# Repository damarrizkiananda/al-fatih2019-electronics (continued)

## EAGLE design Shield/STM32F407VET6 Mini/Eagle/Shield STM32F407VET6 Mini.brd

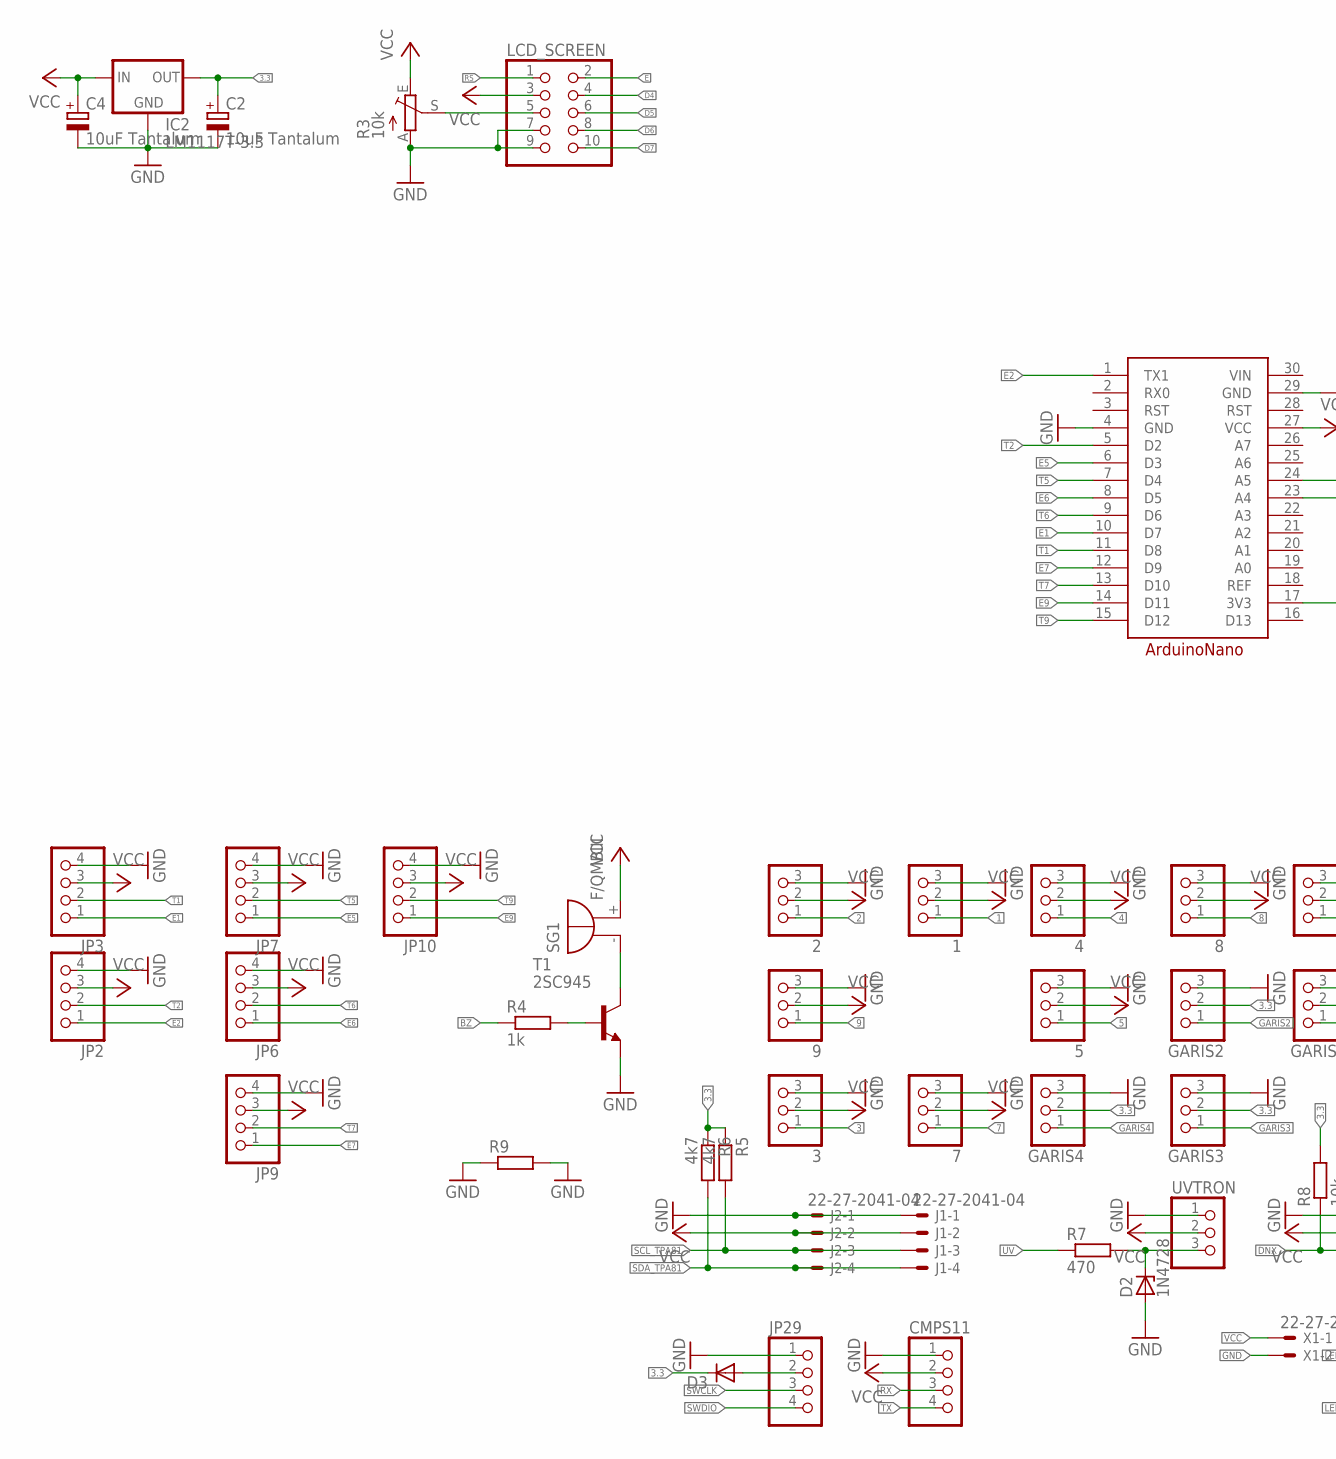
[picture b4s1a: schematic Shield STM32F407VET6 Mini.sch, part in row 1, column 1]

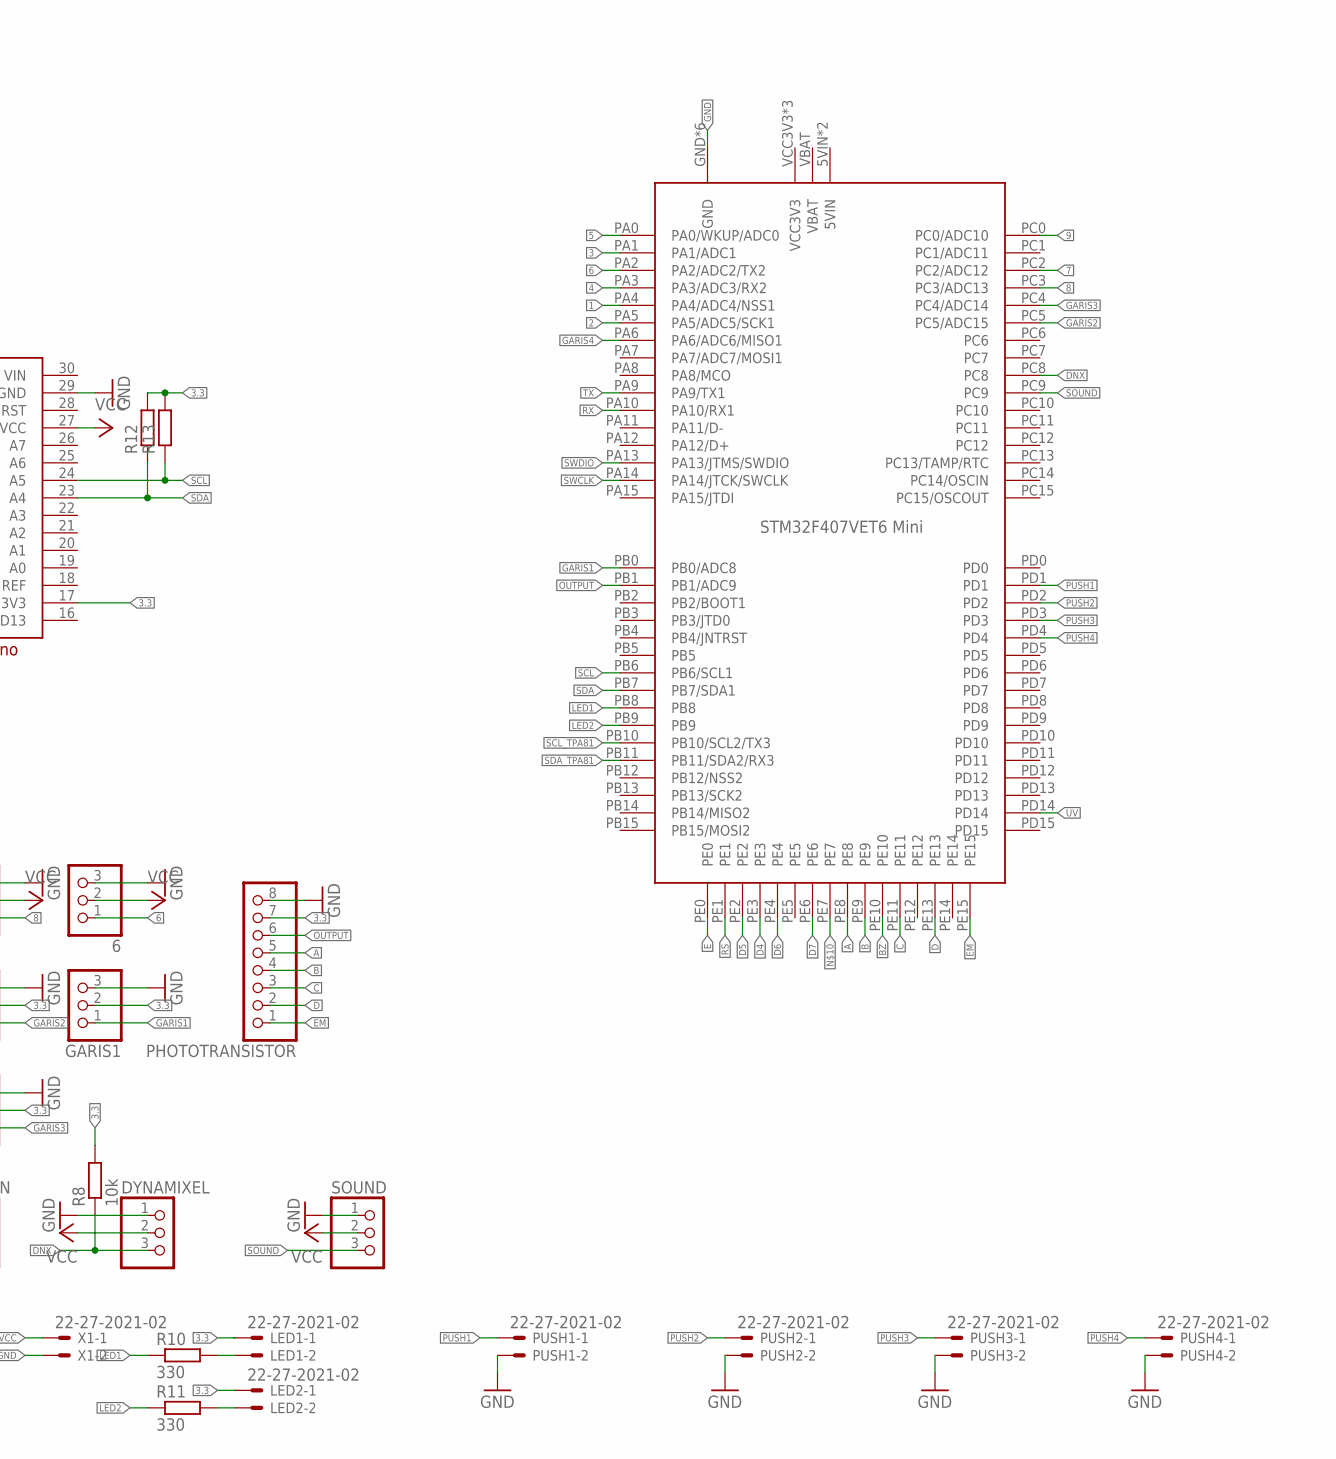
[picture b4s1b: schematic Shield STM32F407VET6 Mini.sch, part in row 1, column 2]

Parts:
1, 2, 3, 4, 5, 6, 7, 8, 9: PINHD-1X3; 1X03
A1: ARDUINONANO
C2, C4: 10uF Tantalum; E2,5-5
CMPS11: PINHD-1X4; 1X04
D2: 1N4728; ZDIO-7.5
D3: DIODE-DO34-7; DO34-7
DYNAMIXEL: PINHD-1X3; 1X03
GARIS1, GARIS2, GARIS3, GARIS4: PINHD-1X3; 1X03
IC2: LM1117T-3.3; TO220
J1, J2: 22-27-2041-04; 6410-04
JP2, JP3, JP6, JP7, JP9, JP10, JP29: PINHD-1X4; 1X04
LCD_SCREEN: PINHD-2X5; 2X05
LED1, LED2: 22-27-2021-02; 6410-02
PHOTOTRANSISTOR: PINHD-1X8; 1X08
PUSH1, PUSH2, PUSH3, PUSH4: 22-27-2021-02; 6410-02
R3: 10k; CA6V
R4: 1k; 0204/7
R5, R6: 4k7; 0204/7
R7: 470; 0204/7
R8: 10k; 0204/7
R9: R-EU_0204/5; 0204/5
R10, R11: 330; M1206
R12, R13: R-EU_0204/7; 0204/7
SG1: F/QMBIII
SOUND: PINHD-1X3; 1X03
T1: 2SC945; TO92-ECB
U$2: STM32F407VET6_MINI
UVTRON: PINHD-1X3; 1X03
X1: 22-27-2021-02; 6410-02

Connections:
1: 1.1, U$2.PA4 (PA4/ADC4/NSS1)
2: 2.1, U$2.PA5 (PA5/ADC5/SCK1)
3: 3.1, U$2.PA1 (PA1/ADC1)
3.3: A1.17 (3V3), C2.+, D3.C, GARIS1.2, GARIS2.2, GARIS3.2, GARIS4.2, IC2.2 (OUT), LED1.1, LED2.1, PHOTOTRANSISTOR.7, R5.1, R6.1, R8.2, R12.2, R13.2
4: 4.1, U$2.PA3 (PA3/ADC3/RX2)
5: 5.1, U$2.PA0 (PA0/WKUP/ADC0)
6: 6.1, U$2.PA2 (PA2/ADC2/TX2)
7: 7.1, U$2.PC2 (PC2/ADC12)
8: 8.1, U$2.PC3 (PC3/ADC13)
9: 9.1, U$2.PC0 (PC0/ADC10)
A: PHOTOTRANSISTOR.5, U$2.PE8
B: PHOTOTRANSISTOR.4, U$2.PE9
BZ: R4.1, U$2.PE10
C: PHOTOTRANSISTOR.3, U$2.PE11
D: PHOTOTRANSISTOR.2, U$2.PE13
D4: LCD_SCREEN.4, U$2.PE3
D5: LCD_SCREEN.6, U$2.PE2
D6: LCD_SCREEN.8, U$2.PE4
D7: LCD_SCREEN.10, U$2.PE6
DNX: DYNAMIXEL.3, R8.1, U$2.PC8
E: LCD_SCREEN.2, U$2.PE0
E1: A1.10 (D7), JP3.1
E2: A1.1 (TX1), JP2.1
E5: A1.6 (D3), JP7.1
E6: A1.8 (D5), JP6.1
E7: A1.12 (D9), JP9.1
E9: A1.14 (D11), JP10.1
EM: PHOTOTRANSISTOR.1, U$2.PE15
GARIS1: GARIS1.1, U$2.PB0 (PB0/ADC8)
GARIS2: GARIS2.1, U$2.PC5 (PC5/ADC15)
GARIS3: GARIS3.1, U$2.PC4 (PC4/ADC14)
GARIS4: GARIS4.1, U$2.PA6 (PA6/ADC6/MISO1)
GND: 1.3, 2.3, 3.3, 4.3, 5.3, 6.3, 7.3, 8.3, 9.3, A1.4 (GND), A1.29 (GND), C2.-, C4.-, CMPS11.1, D2.A, DYNAMIXEL.1, GARIS1.3, GARIS2.3, GARIS3.3, GARIS4.3, IC2.1 (GND), J1.1, J2.1, JP2.4, JP3.4, JP6.4, JP7.4, JP9.4, JP10.4, JP29.1, LCD_SCREEN.7, LCD_SCREEN.9, PHOTOTRANSISTOR.8, PUSH1.2, PUSH2.2, PUSH3.2, PUSH4.2, R3.A, R9.1, R9.2, SOUND.1, T1.E, U$2.GND, U$2.GND@1 (GND), U$2.GND@2 (GND), U$2.GND@3 (GND), U$2.GND@4 (GND), U$2.GND@5 (GND), UVTRON.1, X1.2
LED1: R10.1, U$2.PB8
LED2: R11.1, U$2.PB9
unnamed: D3.A, JP29.2
unnamed: LED1.2, R10.2
unnamed: D2.C, R7.2, UVTRON.3
unnamed: LCD_SCREEN.5, R3.S
unnamed: LED2.2, R11.2
unnamed: SG1.- (+), T1.C
unnamed: R4.2, T1.B
OUTPUT: PHOTOTRANSISTOR.6, U$2.PB1 (PB1/ADC9)
PUSH1: PUSH1.1, U$2.PD1
PUSH2: PUSH2.1, U$2.PD2
PUSH3: PUSH3.1, U$2.PD3
PUSH4: PUSH4.1, U$2.PD4
REF: A1.18 (REF)
RS: LCD_SCREEN.1, U$2.PE1
RX: CMPS11.3, U$2.PA10 (PA10/RX1)
SCL: A1.24 (A5), R13.1, U$2.PB6 (PB6/SCL1)
SCL_TPA81: J1.3, J2.3, R5.2, U$2.PB10 (PB10/SCL2/TX3)
SDA: A1.23 (A4), R12.1, U$2.PB7 (PB7/SDA1)
SDA_TPA81: J1.4, J2.4, R6.2, U$2.PB11 (PB11/SDA2/RX3)
SOUND: SOUND.3, U$2.PC9
SWCLK: JP29.3, U$2.PA14 (PA14/JTCK/SWCLK)
SWDIO: JP29.4, U$2.PA13 (PA13/JTMS/SWDIO)
T1: A1.11 (D8), JP3.2
T2: A1.5 (D2), JP2.2
T5: A1.7 (D4), JP7.2
T6: A1.9 (D6), JP6.2
T7: A1.13 (D10), JP9.2
T9: A1.15 (D12), JP10.2
TX: CMPS11.4, U$2.PA9 (PA9/TX1)
UV: R7.1, U$2.PD14
VCC: 1.2, 2.2, 3.2, 4.2, 5.2, 6.2, 7.2, 8.2, 9.2, A1.27 (VCC), C4.+, CMPS11.2, DYNAMIXEL.2, IC2.3 (IN), J1.2, J2.2, JP2.3, JP3.3, JP6.3, JP7.3, JP9.3, JP10.3, LCD_SCREEN.3, R3.E, SG1.+ (-), SOUND.2, UVTRON.2, X1.1
VIN: A1.30 (VIN)

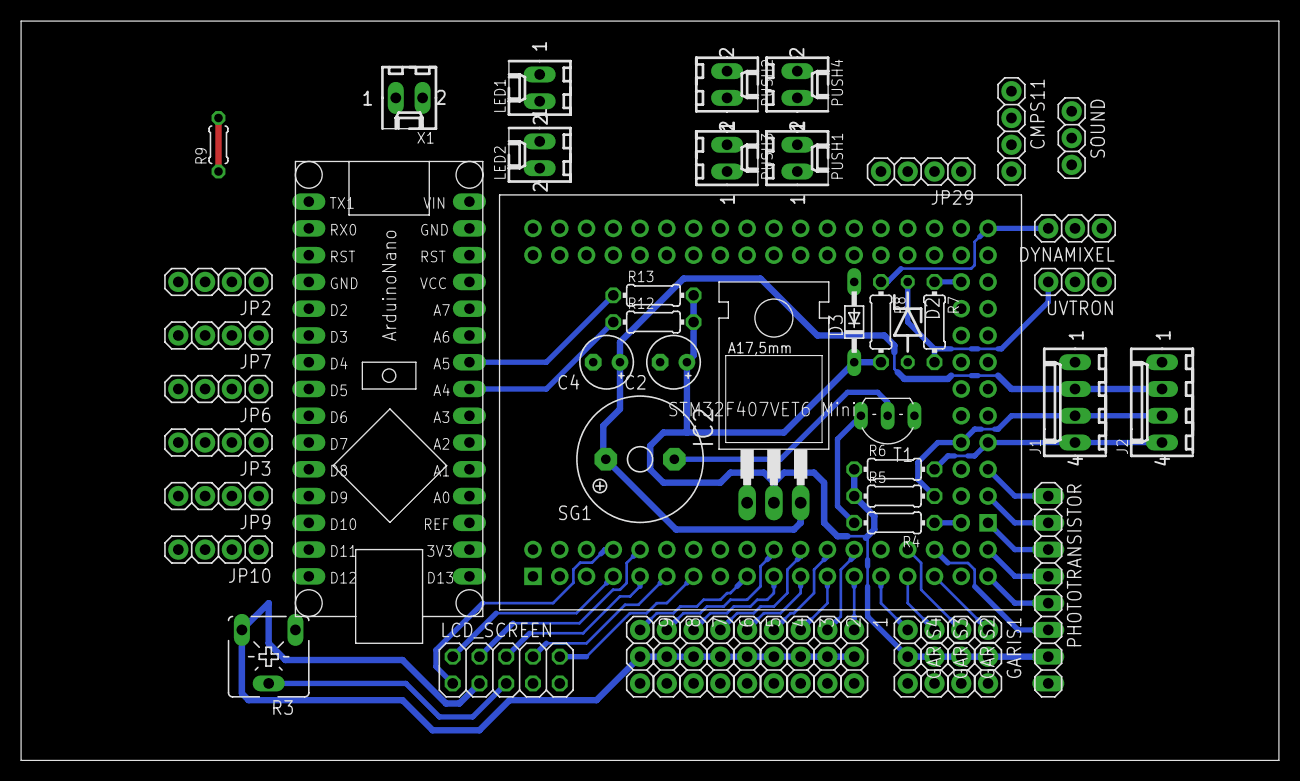
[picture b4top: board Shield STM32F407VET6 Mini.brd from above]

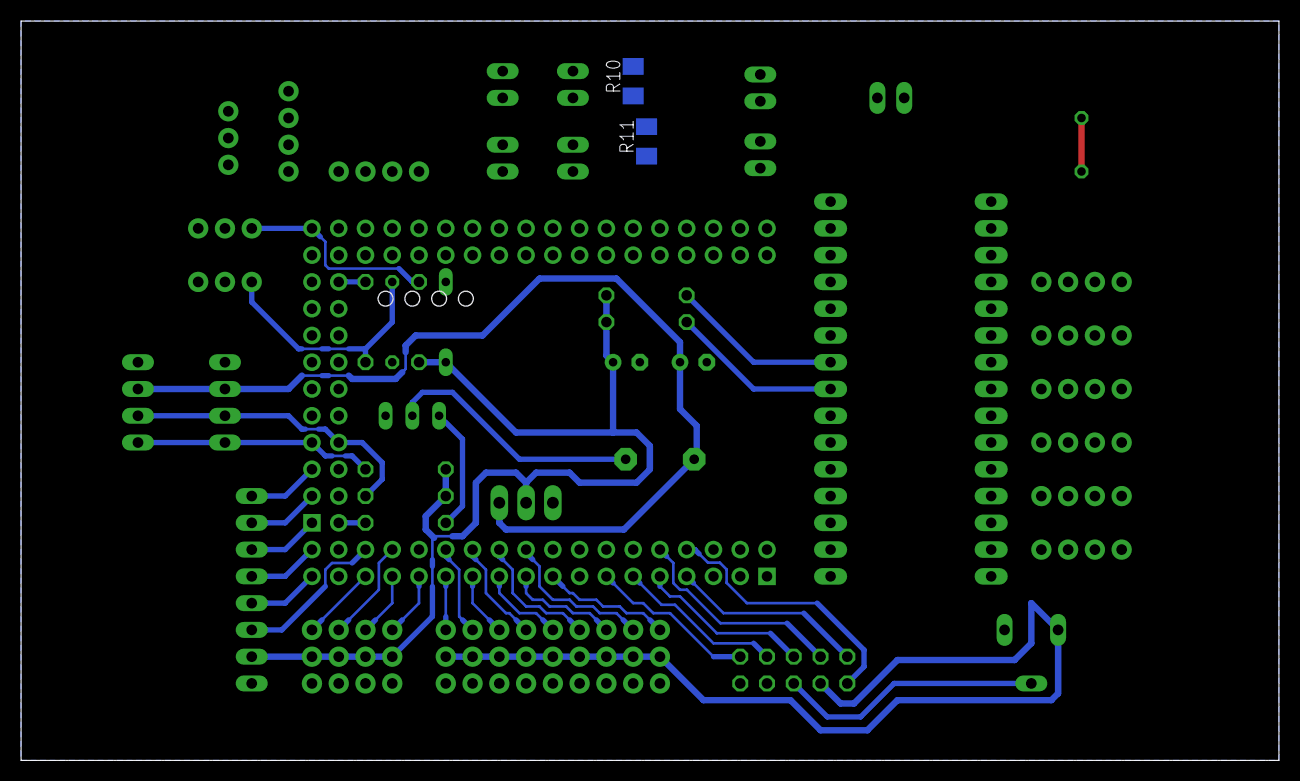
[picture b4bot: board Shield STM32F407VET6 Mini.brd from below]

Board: 2 copper layers, 119.4 x 70.2 mm, 55 parts (2 on the bottom side), 65 nets.

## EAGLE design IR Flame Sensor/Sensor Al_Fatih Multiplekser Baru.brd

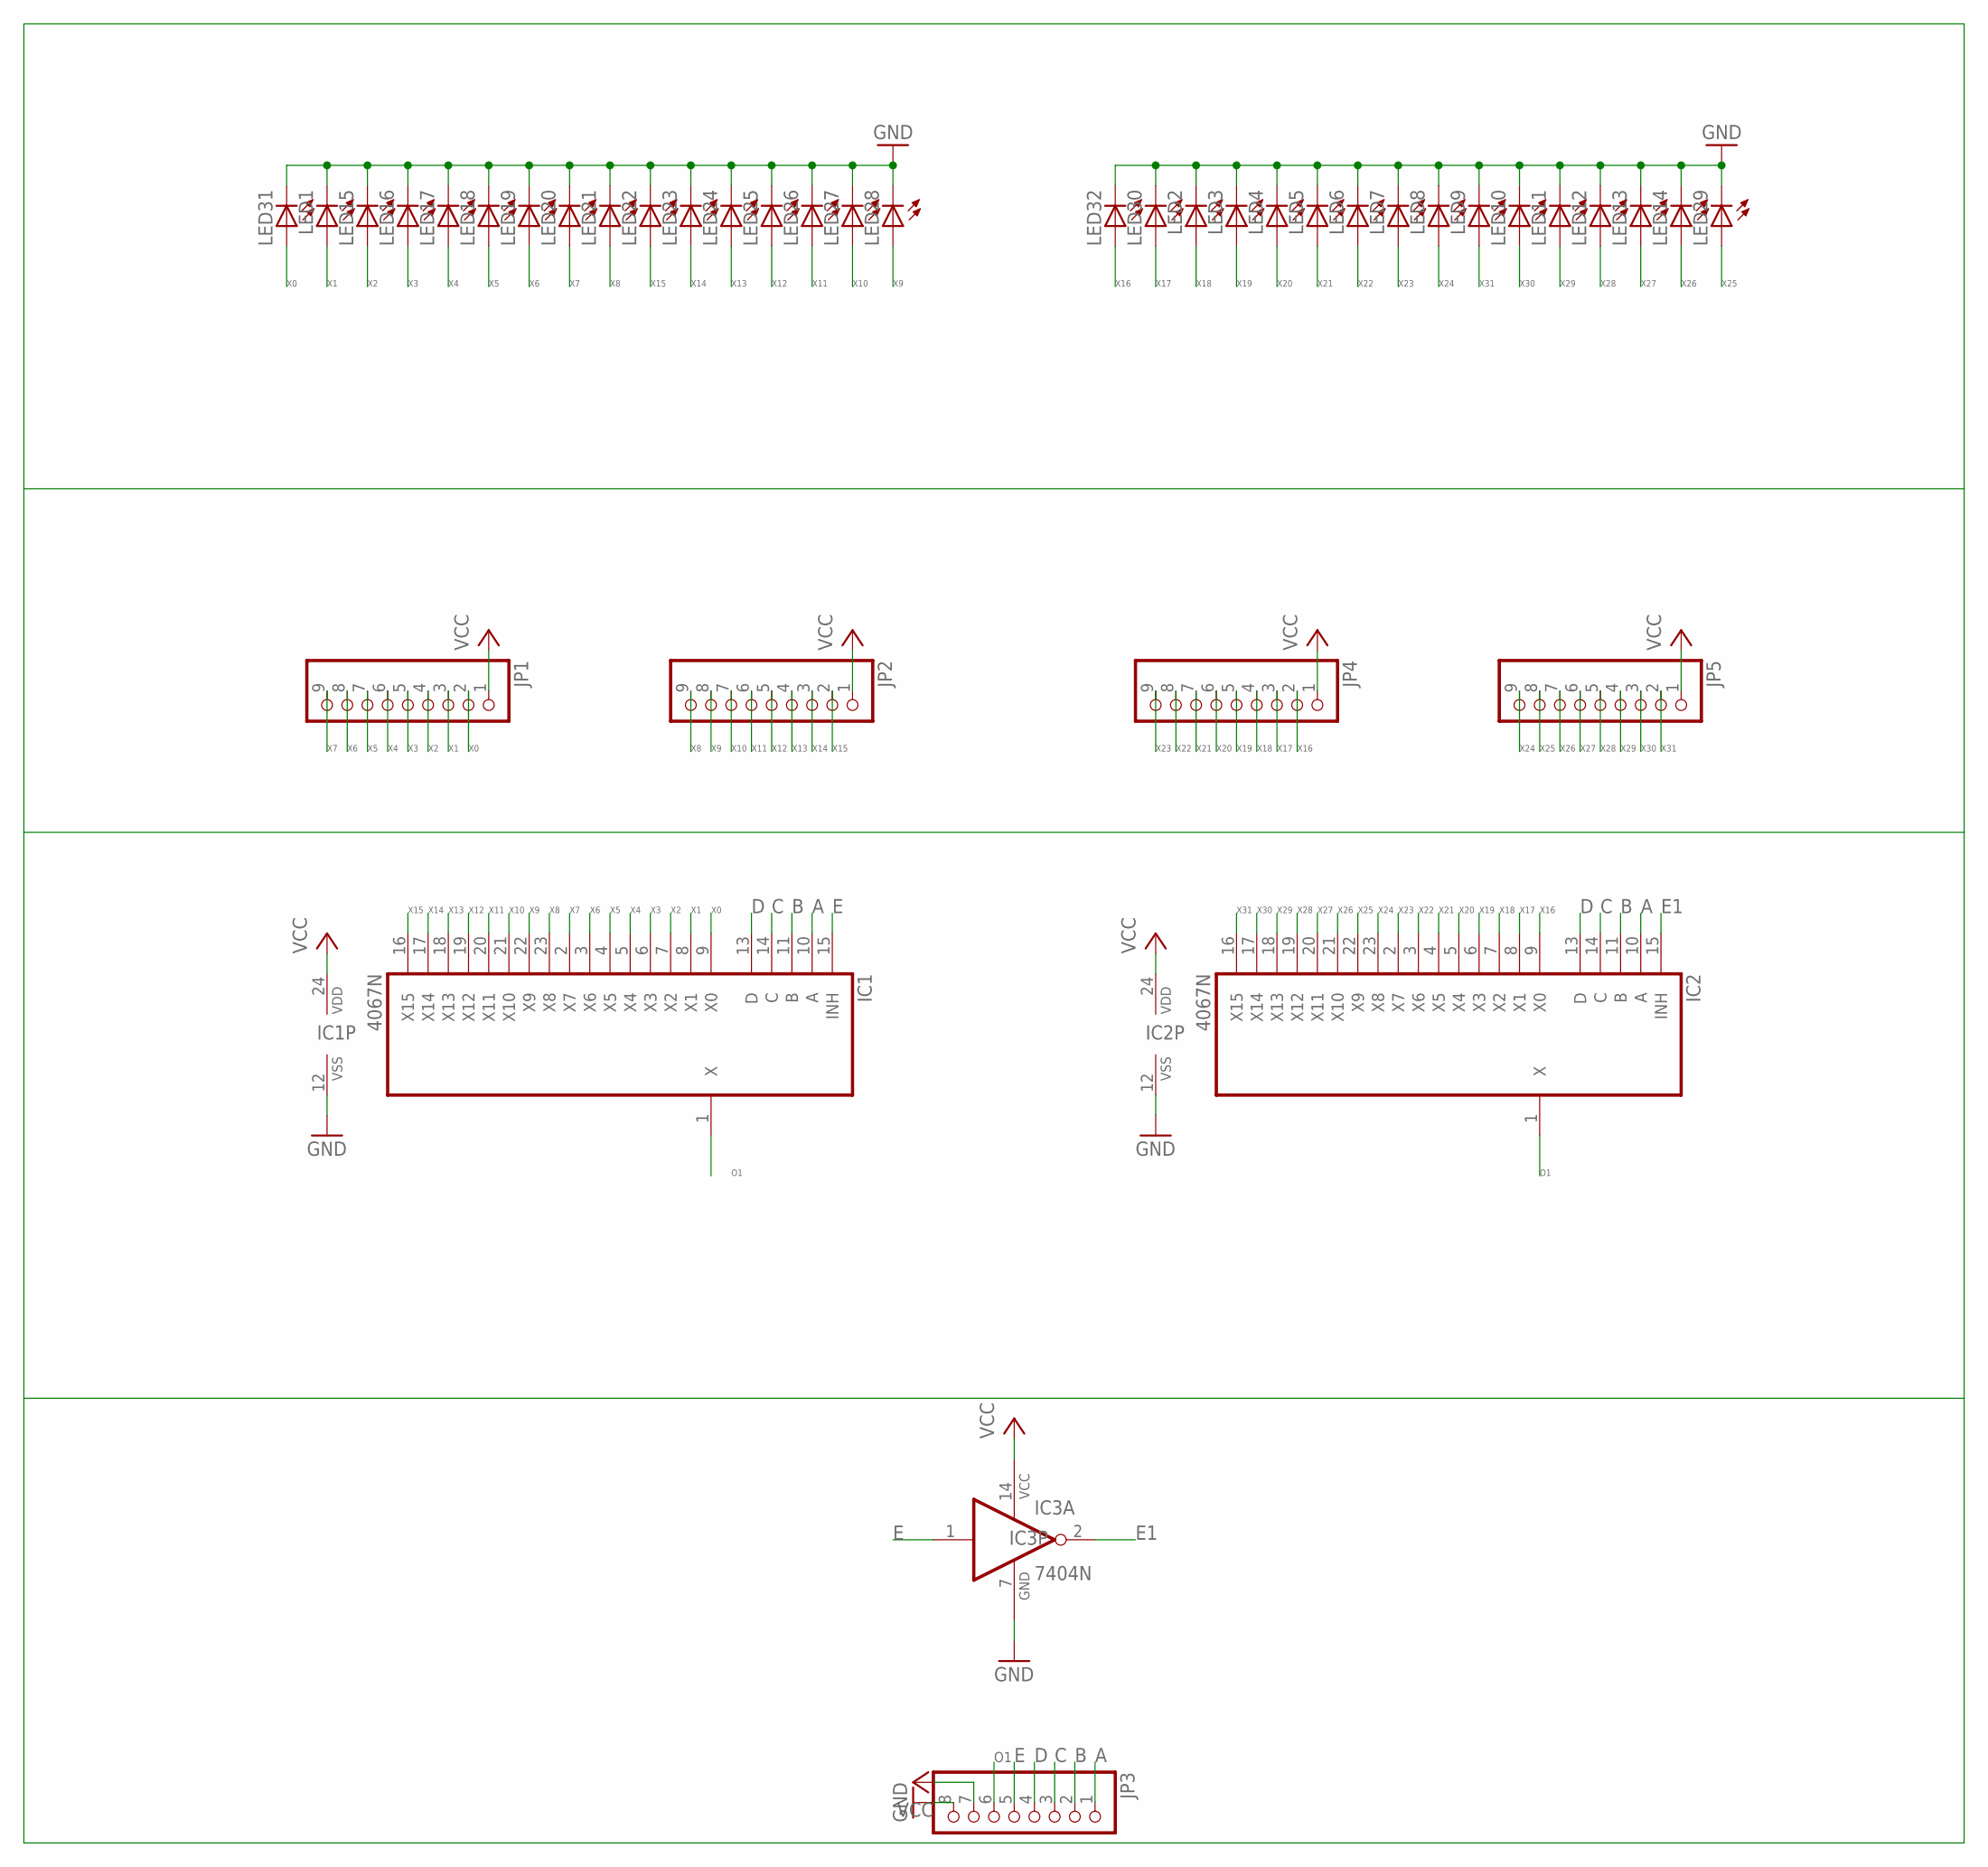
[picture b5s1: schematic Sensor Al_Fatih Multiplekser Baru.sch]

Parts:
IC1, IC2: 4067N; DIL24-6
IC3: 7404N; DIL14
JP1, JP2, JP4, JP5: PINHD-1X9; 1X09
JP3: PINHD-1X8; 1X08
LED1, LED2, LED3, LED4, LED5, LED6, LED7, LED8, LED9, LED10, LED11, LED12, LED13, LED14, LED15, LED16, LED17, LED18, LED19, LED20, LED21, LED22, LED23, LED24, LED25, LED26, LED27, LED28, LED29, LED30, LED31, LED32: LED3MM

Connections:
A: IC1.10 (A), IC2.10 (A), JP3.1
B: IC1.11 (B), IC2.11 (B), JP3.2
C: IC1.14 (C), IC2.14 (C), JP3.3
D: IC1.13 (D), IC2.13 (D), JP3.4
E: IC1.15 (INH), IC3.1 (I), JP3.5
E1: IC2.15 (INH), IC3.2 (O)
GND: IC1.12 (VSS), IC2.12 (VSS), IC3.7 (GND), JP3.8, LED1.K (C), LED2.K (C), LED3.K (C), LED4.K (C), LED5.K (C), LED6.K (C), LED7.K (C), LED8.K (C), LED9.K (C), LED10.K (C), LED11.K (C), LED12.K (C), LED13.K (C), LED14.K (C), LED15.K (C), LED16.K (C), LED17.K (C), LED18.K (C), LED19.K (C), LED20.K (C), LED21.K (C), LED22.K (C), LED23.K (C), LED24.K (C), LED25.K (C), LED26.K (C), LED27.K (C), LED28.K (C), LED29.K (C), LED30.K (C), LED31.K (C), LED32.K (C)
O1: IC1.1 (X), IC2.1 (X), JP3.6
VCC: IC1.24 (VDD), IC2.24 (VDD), IC3.14 (VCC), JP1.1, JP2.1, JP3.7, JP4.1, JP5.1
X0: IC1.9 (X0), JP1.2, LED31.A
X1: IC1.8 (X1), JP1.3, LED1.A
X2: IC1.7 (X2), JP1.4, LED15.A
X3: IC1.6 (X3), JP1.5, LED16.A
X4: IC1.5 (X4), JP1.6, LED17.A
X5: IC1.4 (X5), JP1.7, LED18.A
X6: IC1.3 (X6), JP1.8, LED19.A
X7: IC1.2 (X7), JP1.9, LED20.A
X8: IC1.23 (X8), JP2.9, LED21.A
X9: IC1.22 (X9), JP2.8, LED28.A
X10: IC1.21 (X10), JP2.7, LED27.A
X11: IC1.20 (X11), JP2.6, LED26.A
X12: IC1.19 (X12), JP2.5, LED25.A
X13: IC1.18 (X13), JP2.4, LED24.A
X14: IC1.17 (X14), JP2.3, LED23.A
X15: IC1.16 (X15), JP2.2, LED22.A
X16: IC2.9 (X0), JP4.2, LED32.A
X17: IC2.8 (X1), JP4.3, LED30.A
X18: IC2.7 (X2), JP4.4, LED2.A
X19: IC2.6 (X3), JP4.5, LED3.A
X20: IC2.5 (X4), JP4.6, LED4.A
X21: IC2.4 (X5), JP4.7, LED5.A
X22: IC2.3 (X6), JP4.8, LED6.A
X23: IC2.2 (X7), JP4.9, LED7.A
X24: IC2.23 (X8), JP5.9, LED8.A
X25: IC2.22 (X9), JP5.8, LED29.A
X26: IC2.21 (X10), JP5.7, LED14.A
X27: IC2.20 (X11), JP5.6, LED13.A
X28: IC2.19 (X12), JP5.5, LED12.A
X29: IC2.18 (X13), JP5.4, LED11.A
X30: IC2.17 (X14), JP5.3, LED10.A
X31: IC2.16 (X15), JP5.2, LED9.A

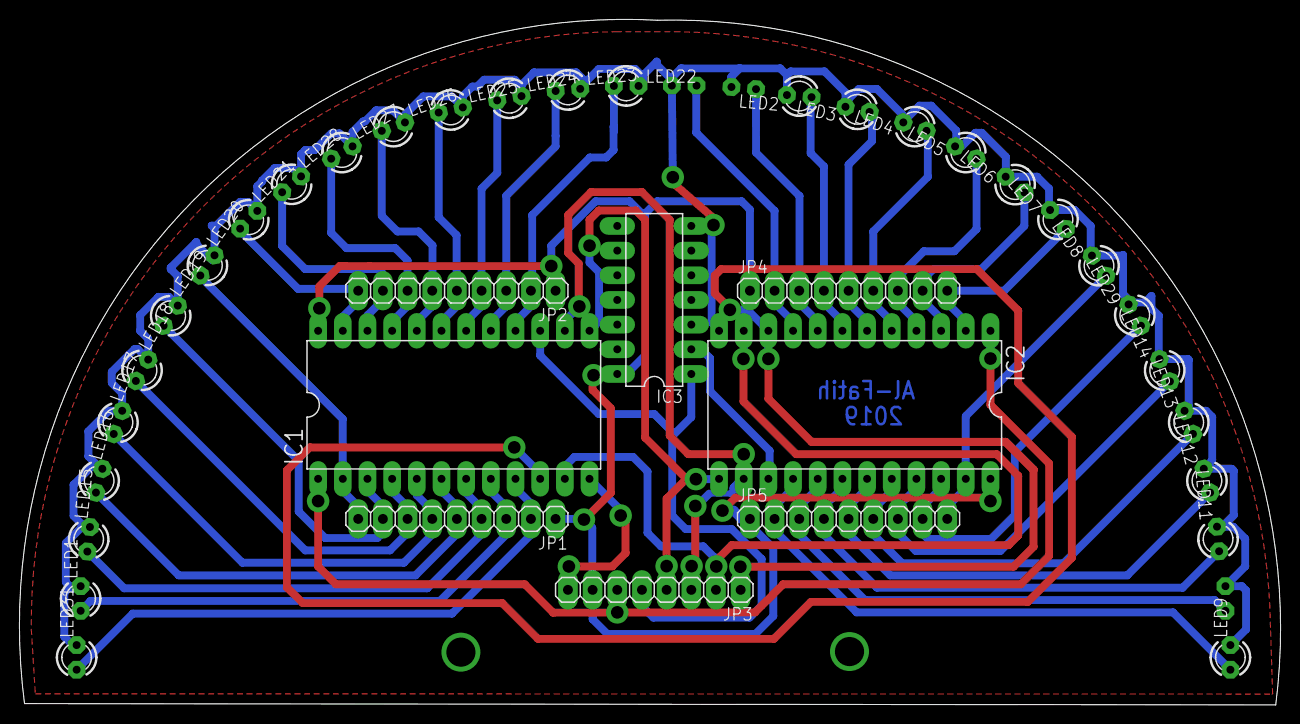
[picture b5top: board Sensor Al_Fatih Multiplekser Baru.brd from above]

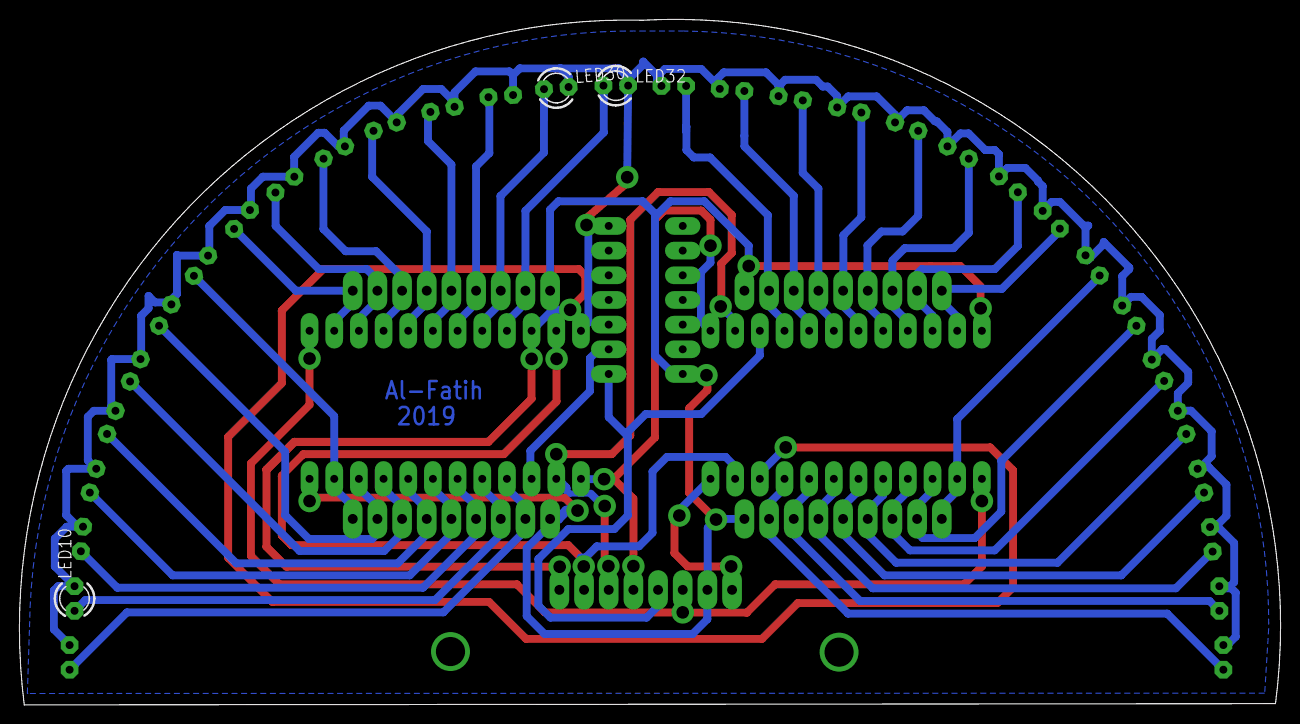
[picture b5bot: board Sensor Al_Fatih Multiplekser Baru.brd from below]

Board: 2 copper layers, 129.8 x 70.6 mm, 40 parts (3 on the bottom side), 41 nets.

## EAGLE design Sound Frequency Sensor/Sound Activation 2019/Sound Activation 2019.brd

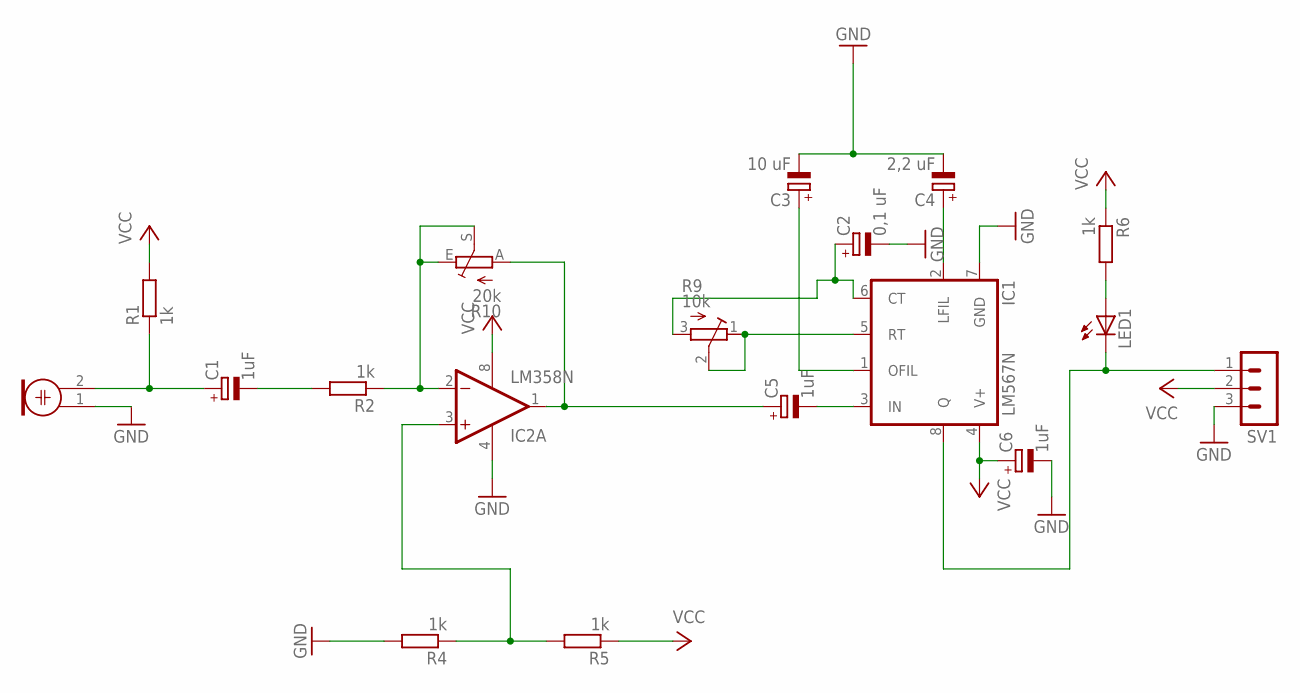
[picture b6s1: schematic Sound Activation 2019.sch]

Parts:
C1, C5, C6: 1uF; E1,8-4
C2: 0,1 uF; E1,8-4
C3: 10 uF; E1,8-4
C4: 2,2 uF; E1,8-4
IC1: LM567N; DIL08
IC2: LM358N; DIL08
LED1: LED3MM
M1: ELECTRET_MICROPHON-F6050AP; F6050AP
R1, R2, R4, R5, R6: 1k; 0204/7
R9: 10k; RTRIM3006P
R10: 20k; CA6V
SV1: MA03-1

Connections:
GND: C2.-, C3.-, C4.-, C6.-, IC1.7 (GND), IC2.4 (V-), M1.1, R4.2, SV1.3
unnamed: IC2.2 (-IN), R2.1, R10.E, R10.S
unnamed: IC2.3 (+IN), R4.1, R5.2
unnamed: C1.+, M1.2, R1.1
unnamed: C1.-, R2.2
unnamed: C2.+, IC1.6 (CT), R9.3 (A)
unnamed: IC1.5 (RT), R9.1 (E), R9.2 (S)
unnamed: C5.+, IC2.1 (OUT), R10.A
unnamed: IC1.8 (Q), LED1.K (C), SV1.1
unnamed: LED1.A, R6.2
unnamed: C5.-, IC1.3 (IN)
unnamed: C3.+, IC1.1 (OFIL)
unnamed: C4.+, IC1.2 (LFIL)
VCC: C6.+, IC1.4 (V+), IC2.8 (V+), R1.2, R5.1, R6.1, SV1.2

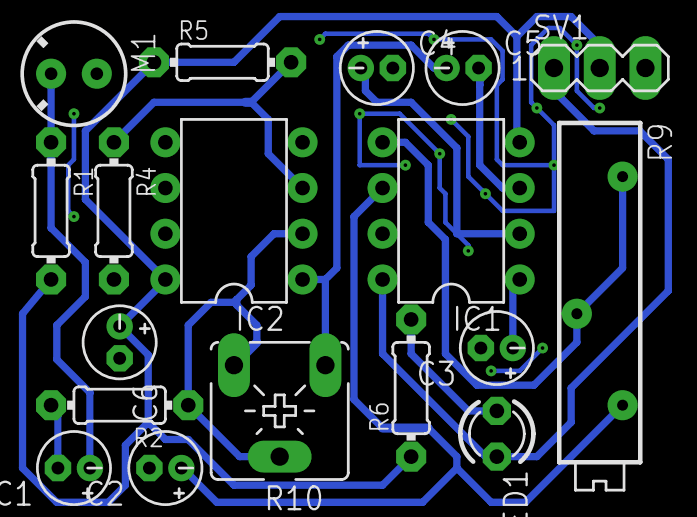
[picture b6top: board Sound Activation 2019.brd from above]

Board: 2 copper layers, 18 parts (0 on the bottom side), 14 nets.

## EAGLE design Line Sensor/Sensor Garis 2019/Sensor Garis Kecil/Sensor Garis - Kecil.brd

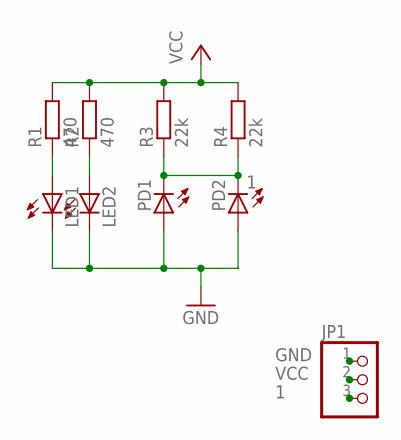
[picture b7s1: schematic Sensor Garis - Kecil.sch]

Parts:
JP1: PINHD-1X3; 1X03
LED1, LED2: LED3MM
PD1, PD2: LED3MM
R1, R2: 470; M0805
R3, R4: 22k; M0805

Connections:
1: JP1.3, PD1.K (C), PD2.K (C), R3.1, R4.1
GND: JP1.1, LED1.K (C), LED2.K (C), PD1.A, PD2.A
unnamed: LED2.A, R2.1
unnamed: LED1.A, R1.1
VCC: JP1.2, R1.2, R2.2, R3.2, R4.2

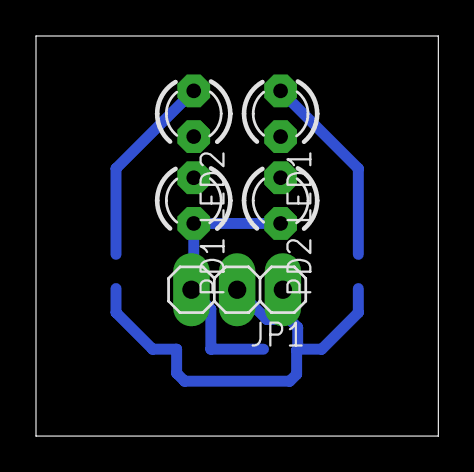
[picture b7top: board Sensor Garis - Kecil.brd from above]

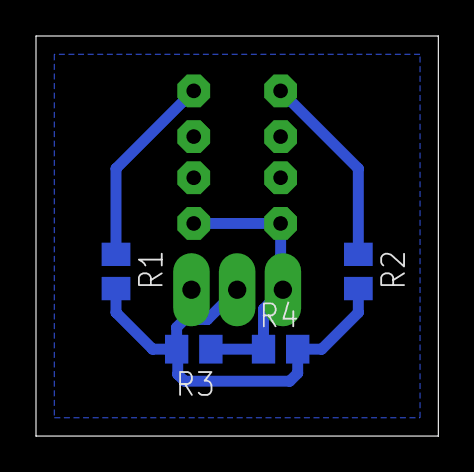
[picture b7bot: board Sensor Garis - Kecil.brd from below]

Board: 2 copper layers, 22.4 x 22.2 mm, 9 parts (4 on the bottom side), 5 nets.

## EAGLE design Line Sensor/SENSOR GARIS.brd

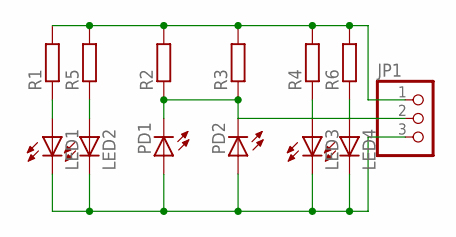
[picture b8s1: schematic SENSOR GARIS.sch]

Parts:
JP1: PINHD-1X3; 1X03
LED1, LED2, LED3, LED4: LED3MM
PD1, PD2: LED3MM
R1, R2, R3, R4, R5, R6: R-EU_M0805; M0805

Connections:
unnamed: JP1.3, LED1.K (C), LED2.K (C), LED3.K (C), LED4.K (C), PD1.A, PD2.A
unnamed: LED1.A, R1.1
unnamed: JP1.2, PD1.K (C), PD2.K (C), R2.1, R3.1
unnamed: LED2.A, R5.1
unnamed: LED3.A, R4.1
unnamed: LED4.A, R6.1
unnamed: JP1.1, R1.2, R2.2, R3.2, R4.2, R5.2, R6.2

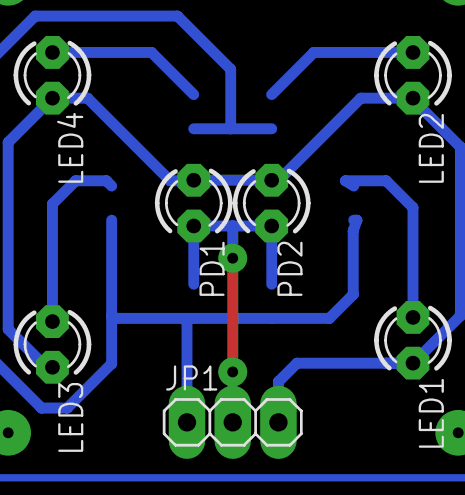
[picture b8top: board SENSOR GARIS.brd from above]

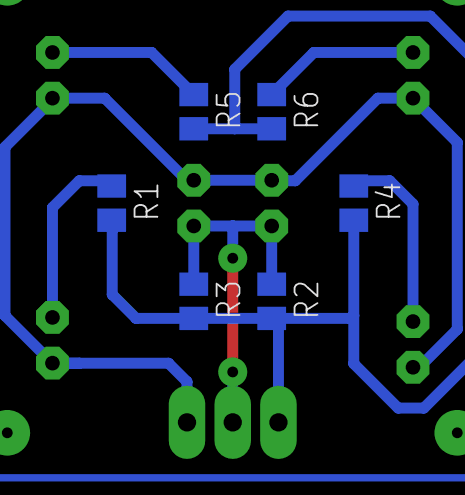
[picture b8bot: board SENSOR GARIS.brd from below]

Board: 2 copper layers, 13 parts (6 on the bottom side), 7 nets.

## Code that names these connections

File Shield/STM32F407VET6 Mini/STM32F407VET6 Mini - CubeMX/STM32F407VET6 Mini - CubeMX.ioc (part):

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Mcu.Name=STM32F407V(E-G)Tx
Mcu.Package=LQFP100
Mcu.UserName=STM32F407VETx
PA1.Mode=Asynchronous
PA1.Signal=UART4_RX
PA10.Mode=Asynchronous
PA10.Signal=USART1_RX
PA4.Signal=ADCx_IN4
PA5.Signal=ADCx_IN5
PA8.Mode=I2C
PA8.Signal=I2C3_SCL
PA9.Mode=Asynchronous
PA9.Signal=USART1_TX
PB6.Mode=I2C
PB6.Signal=I2C1_SCL
PB7.Mode=I2C
PB7.Signal=I2C1_SDA
PC10.Mode=Asynchronous
PC10.Signal=UART4_TX
PC9.Mode=I2C
PC9.Signal=I2C3_SDA
RCC.HSE_VALUE=25000000
RCC.SYSCLKFreq_VALUE=16000000
board=custom

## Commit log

2023-11-07 Upload to GitHub
2023-11-13 Image upload
